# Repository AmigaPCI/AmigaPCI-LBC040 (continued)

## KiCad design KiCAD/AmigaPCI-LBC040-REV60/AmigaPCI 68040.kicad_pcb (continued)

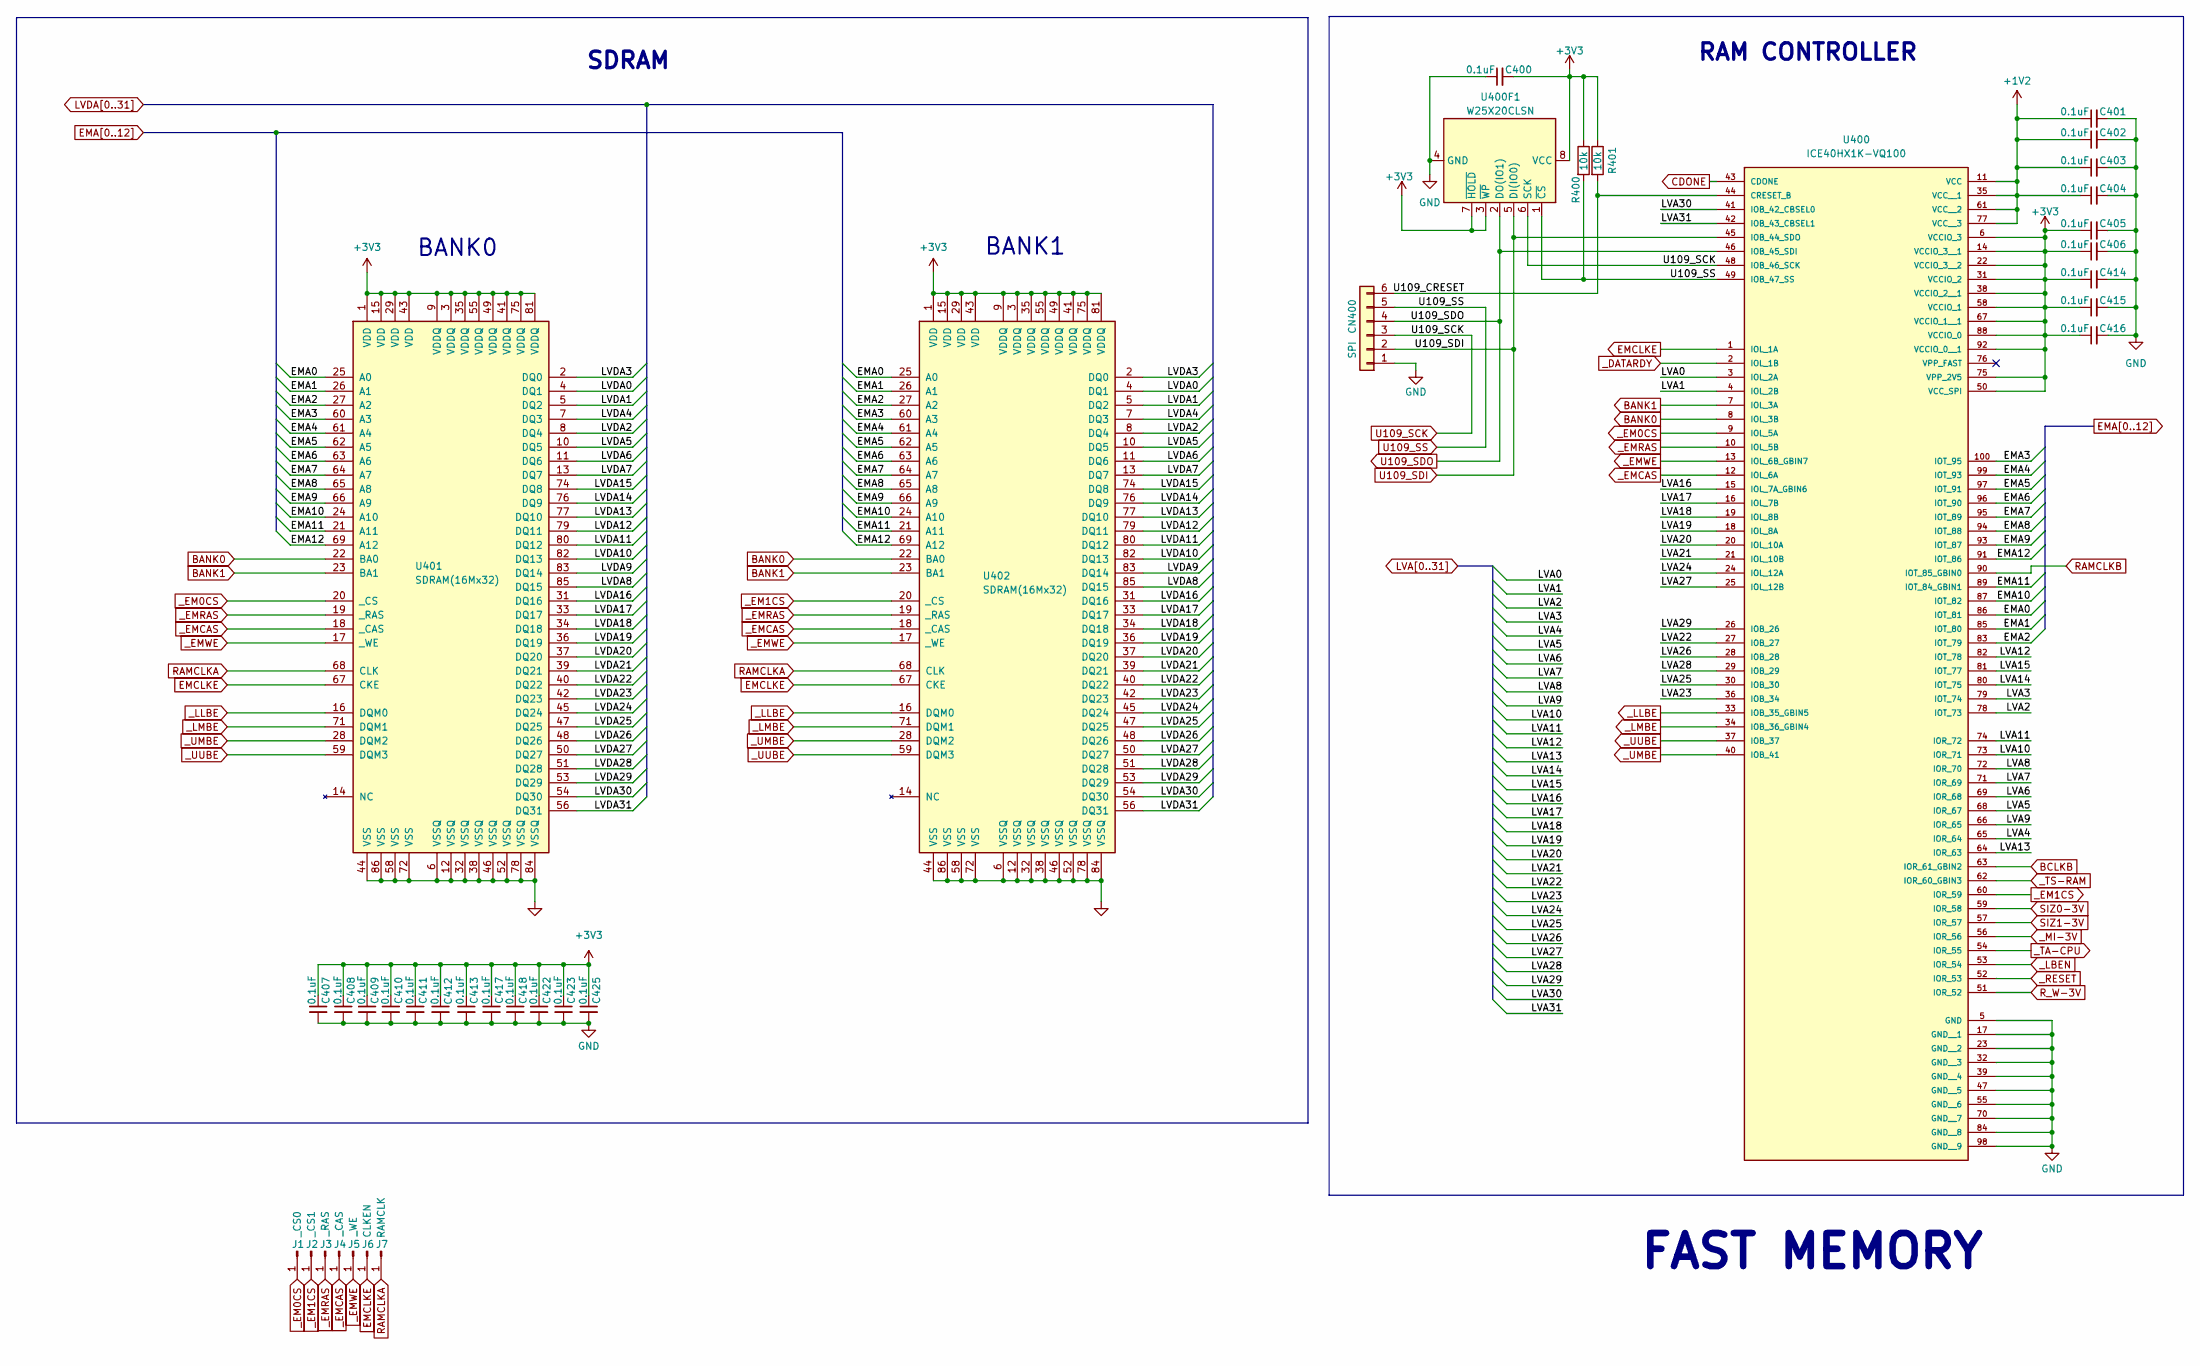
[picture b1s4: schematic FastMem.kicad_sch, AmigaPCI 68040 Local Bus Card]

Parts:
C400, C401, C402, C403, C404, C405, C406, C407, C408, C409, C410, C411, C412, C413, C414, C415, C416, C417, C418, C422, C423, C425: 0.1uF; C_0603_1608Metric; LCSC C14663
CN400: SPI; PinHeader_1x06_P2.54mm_Vertical; LCSC C37208
J1: _CS0; TestPoint_Pad_D1.0mm
J2: _CS1; TestPoint_Pad_D1.0mm
J3: _RAS; TestPoint_Pad_D1.0mm
J4: _CAS; TestPoint_Pad_D1.0mm
J5: _WE; TestPoint_Pad_D1.0mm
J6: CLKEN; TestPoint_Pad_D1.0mm
J7: RAMCLK; TestPoint_Pad_D1.0mm
R400, R401: 10k; R_0603_1608Metric; LCSC C25804
U400: ICE40HX1K-VQ100; LQFP-100_14x14mm_P0.5mm; PARTREV 3.4; LCSC C1519043
U400F1: W25X20CLSN; SOIC-8_3.9x4.9mm_P1.27mm; LCSC C34591
U401, U402: SDRAM(16Mx32); TSOP-II-86; LCSC C17489827

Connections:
+1V2: C401.1, C402.1, C403.1, C404.1, U400.11 (VCC), U400.35 (VCC__1), U400.61 (VCC__2), U400.77 (VCC__3); also elsewhere on the board
+3V3: C400.2, C405.1, C406.1, C407.1, C408.1, C409.1, C410.1, C411.1, C412.1, C413.1, C414.1, C415.1, C416.1, C417.1, C418.1, C422.1, C423.1, C425.1, R400.1, R401.1, U400.6 (VCCIO_3), U400.14 (VCCIO_3__1), U400.22 (VCCIO_3__2), U400.31 (VCCIO_2), U400.38 (VCCIO_2__1), U400.50 (VCC_SPI), U400.58 (VCCIO_1), U400.67 (VCCIO_1__1), U400.75 (VPP_2V5), U400.88 (VCCIO_0), U400.92 (VCCIO_0__1), U400F1.3 (~WP), U400F1.7 (~HOLD), U400F1.8 (VCC), U401.1 (VDD), U401.3 (VDDQ), U401.9 (VDDQ), U401.15 (VDD), U401.29 (VDD), U401.35 (VDDQ), U401.41 (VDDQ), U401.43 (VDD), U401.49 (VDDQ), U401.55 (VDDQ), U401.75 (VDDQ), U401.81 (VDDQ), U402.1 (VDD), U402.3 (VDDQ), U402.9 (VDDQ), U402.15 (VDD), U402.29 (VDD), U402.35 (VDDQ), U402.41 (VDDQ), U402.43 (VDD), U402.49 (VDDQ), U402.55 (VDDQ), U402.75 (VDDQ), U402.81 (VDDQ); also elsewhere on the board
/Fast Memory/U109_CRESET: CN400.6, R401.2, U400.44 (CRESET_B)
BANK0: U400.8 (IOL_3B), U401.22 (BA0), U402.22 (BA0)
BANK1: U400.7 (IOL_3A), U401.23 (BA1), U402.23 (BA1)
BCLKB: U400.63 (IOR_61_GBIN2); also elsewhere on the board
CDONE: U400.43 (CDONE); also elsewhere on the board
EMA0: U400.86 (IOT_81), U401.25 (A0), U402.25 (A0)
EMA1: U400.85 (IOT_80), U401.26 (A1), U402.26 (A1)
EMA2: U400.83 (IOT_79), U401.27 (A2), U402.27 (A2)
EMA3: U400.100 (IOT_95), U401.60 (A3), U402.60 (A3)
EMA4: U400.99 (IOT_93), U401.61 (A4), U402.61 (A4)
EMA5: U400.97 (IOT_91), U401.62 (A5), U402.62 (A5)
EMA6: U400.96 (IOT_90), U401.63 (A6), U402.63 (A6)
EMA7: U400.95 (IOT_89), U401.64 (A7), U402.64 (A7)
EMA8: U400.94 (IOT_88), U401.65 (A8), U402.65 (A8)
EMA9: U400.93 (IOT_87), U401.66 (A9), U402.66 (A9)
EMA10: U400.87 (IOT_82), U401.24 (A10), U402.24 (A10)
EMCLKE: J6.1, U400.1 (IOL_1A), U401.67 (CKE), U402.67 (CKE)
GND: C400.1, C401.2, C402.2, C403.2, C404.2, C405.2, C406.2, C407.2, C408.2, C409.2, C410.2, C411.2, C412.2, C413.2, C414.2, C415.2, C416.2, C417.2, C418.2, C422.2, C423.2, C425.2, CN400.1, U400.5 (GND), U400.17 (GND__1), U400.23 (GND__2), U400.32 (GND__3), U400.39 (GND__4), U400.47 (GND__5), U400.55 (GND__6), U400.70 (GND__7), U400.84 (GND__8), U400.98 (GND__9), U400F1.4 (GND), U401.6 (VSSQ), U401.12 (VSSQ), U401.32 (VSSQ), U401.38 (VSSQ), U401.44 (VSS), U401.46 (VSSQ), U401.52 (VSSQ), U401.58 (VSS), U401.72 (VSS), U401.78 (VSSQ), U401.84 (VSSQ), U401.86 (VSS), U402.6 (VSSQ), U402.12 (VSSQ), U402.32 (VSSQ), U402.38 (VSSQ), U402.44 (VSS), U402.46 (VSSQ), U402.52 (VSSQ), U402.58 (VSS), U402.72 (VSS), U402.78 (VSSQ), U402.84 (VSSQ), U402.86 (VSS); also elsewhere on the board
LVA0: U400.3 (IOL_2A); also elsewhere on the board
LVA1: U400.4 (IOL_2B); also elsewhere on the board
LVA2: U400.78 (IOT_73); also elsewhere on the board
LVA3: U400.79 (IOT_74); also elsewhere on the board
LVA4: U400.65 (IOR_64); also elsewhere on the board
LVA5: U400.68 (IOR_67); also elsewhere on the board
LVA6: U400.69 (IOR_68); also elsewhere on the board
LVA7: U400.71 (IOR_69); also elsewhere on the board
LVA8: U400.72 (IOR_70); also elsewhere on the board
LVA9: U400.66 (IOR_65); also elsewhere on the board
LVA10: U400.73 (IOR_71); also elsewhere on the board
LVA11: U400.74 (IOR_72); also elsewhere on the board
LVA12: U400.82 (IOT_78); also elsewhere on the board
LVA13: U400.64 (IOR_63); also elsewhere on the board
LVA14: U400.80 (IOT_75); also elsewhere on the board
LVA15: U400.81 (IOT_77); also elsewhere on the board
LVA16: U400.15 (IOL_7A_GBIN6); also elsewhere on the board
LVA17: U400.16 (IOL_7B); also elsewhere on the board
LVA18: U400.19 (IOL_8B); also elsewhere on the board
LVA19: U400.18 (IOL_8A); also elsewhere on the board
LVA20: U400.20 (IOL_10A); also elsewhere on the board
LVA21: U400.21 (IOL_10B); also elsewhere on the board
LVA22: U400.27 (IOB_27); also elsewhere on the board
LVA23: U400.36 (IOB_34); also elsewhere on the board
LVA24: U400.24 (IOL_12A); also elsewhere on the board
LVA25: U400.30 (IOB_30); also elsewhere on the board
LVA26: U400.28 (IOB_28); also elsewhere on the board
LVA27: U400.25 (IOL_12B); also elsewhere on the board
LVA28: U400.29 (IOB_29); also elsewhere on the board
LVA29: U400.26 (IOB_26); also elsewhere on the board
LVA30: U400.41 (IOB_42_CBSEL0); also elsewhere on the board
LVA31: U400.42 (IOB_43_CBSEL1); also elsewhere on the board
LVDA0: U401.4 (DQ1), U402.4 (DQ1); also elsewhere on the board
LVDA1: U401.5 (DQ2), U402.5 (DQ2); also elsewhere on the board
LVDA2: U401.8 (DQ4), U402.8 (DQ4); also elsewhere on the board
LVDA3: U401.2 (DQ0), U402.2 (DQ0); also elsewhere on the board
LVDA4: U401.7 (DQ3), U402.7 (DQ3); also elsewhere on the board
LVDA5: U401.10 (DQ5), U402.10 (DQ5); also elsewhere on the board
LVDA6: U401.11 (DQ6), U402.11 (DQ6); also elsewhere on the board
LVDA7: U401.13 (DQ7), U402.13 (DQ7); also elsewhere on the board
LVDA8: U401.85 (DQ15), U402.85 (DQ15); also elsewhere on the board
LVDA9: U401.83 (DQ14), U402.83 (DQ14); also elsewhere on the board
LVDA10: U401.82 (DQ13), U402.82 (DQ13); also elsewhere on the board
LVDA11: U401.80 (DQ12), U402.80 (DQ12); also elsewhere on the board
LVDA12: U401.79 (DQ11), U402.79 (DQ11); also elsewhere on the board
LVDA13: U401.77 (DQ10), U402.77 (DQ10); also elsewhere on the board
LVDA14: U401.76 (DQ9), U402.76 (DQ9); also elsewhere on the board
LVDA15: U401.74 (DQ8), U402.74 (DQ8); also elsewhere on the board
LVDA16: U401.31 (DQ16), U402.31 (DQ16); also elsewhere on the board
LVDA17: U401.33 (DQ17), U402.33 (DQ17); also elsewhere on the board
LVDA18: U401.34 (DQ18), U402.34 (DQ18); also elsewhere on the board
LVDA19: U401.36 (DQ19), U402.36 (DQ19); also elsewhere on the board
LVDA20: U401.37 (DQ20), U402.37 (DQ20); also elsewhere on the board
LVDA21: U401.39 (DQ21), U402.39 (DQ21); also elsewhere on the board
LVDA22: U401.40 (DQ22), U402.40 (DQ22); also elsewhere on the board
LVDA23: U401.42 (DQ23), U402.42 (DQ23); also elsewhere on the board
LVDA24: U401.45 (DQ24), U402.45 (DQ24); also elsewhere on the board
LVDA25: U401.47 (DQ25), U402.47 (DQ25); also elsewhere on the board
LVDA26: U401.48 (DQ26), U402.48 (DQ26); also elsewhere on the board
LVDA27: U401.50 (DQ27), U402.50 (DQ27); also elsewhere on the board
LVDA28: U401.51 (DQ28), U402.51 (DQ28); also elsewhere on the board
LVDA29: U401.53 (DQ29), U402.53 (DQ29); also elsewhere on the board
LVDA30: U401.54 (DQ30), U402.54 (DQ30); also elsewhere on the board
LVDA31: U401.56 (DQ31), U402.56 (DQ31); also elsewhere on the board
RAMCLKA: J7.1, U401.68 (CLK), U402.68 (CLK); also elsewhere on the board
RAMCLKB: U400.90 (IOT_85_GBIN0); also elsewhere on the board
R_W-3V: U400.51 (IOR_52); also elsewhere on the board
SIZ0-3V: U400.59 (IOR_58); also elsewhere on the board
SIZ1-3V: U400.57 (IOR_57); also elsewhere on the board
U109_SCK: CN400.3, U400.48 (IOB_46_SCK), U400F1.6 (SCK); also elsewhere on the board
U109_SDI: CN400.2, U400.45 (IOB_44_SDO), U400F1.5 (DI(IO0)); also elsewhere on the board
U109_SDO: CN400.4, U400.46 (IOB_45_SDI), U400F1.2 (DO(IO1)); also elsewhere on the board
U109_SS: CN400.5, R400.2, U400.49 (IOB_47_SS), U400F1.1 (~CS); also elsewhere on the board
_DATARDY: U400.2 (IOL_1B); also elsewhere on the board
_EM0CS: J1.1, U400.9 (IOL_5A), U401.20 (_CS)
_EM1CS: J2.1, U400.60 (IOR_59), U402.20 (_CS)
_EMCAS: J4.1, U400.12 (IOL_6A), U401.18 (_CAS), U402.18 (_CAS)
_EMRAS: J3.1, U400.10 (IOL_5B), U401.19 (_RAS), U402.19 (_RAS)
_EMWE: J5.1, U400.13 (IOL_6B_GBIN7), U401.17 (_WE), U402.17 (_WE)
_LBEN: U400.53 (IOR_54); also elsewhere on the board
_LLBE: U400.33 (IOB_35_GBIN5), U401.16 (DQM0), U402.16 (DQM0)
_LMBE: U400.34 (IOB_36_GBIN4), U401.71 (DQM1), U402.71 (DQM1)
_MI-3V: U400.56 (IOR_56); also elsewhere on the board
_RESET: U400.52 (IOR_53); also elsewhere on the board
_TA-CPU: U400.54 (IOR_55); also elsewhere on the board
_TS-RAM: U400.62 (IOR_60_GBIN3); also elsewhere on the board
_UMBE: U400.40 (IOB_41), U401.28 (DQM2), U402.28 (DQM2)
_UUBE: U400.37 (IOB_37), U401.59 (DQM3), U402.59 (DQM3)

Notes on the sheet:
RAM CONTROLLER
FAST MEMORY
BANK0
SDRAM
BANK1

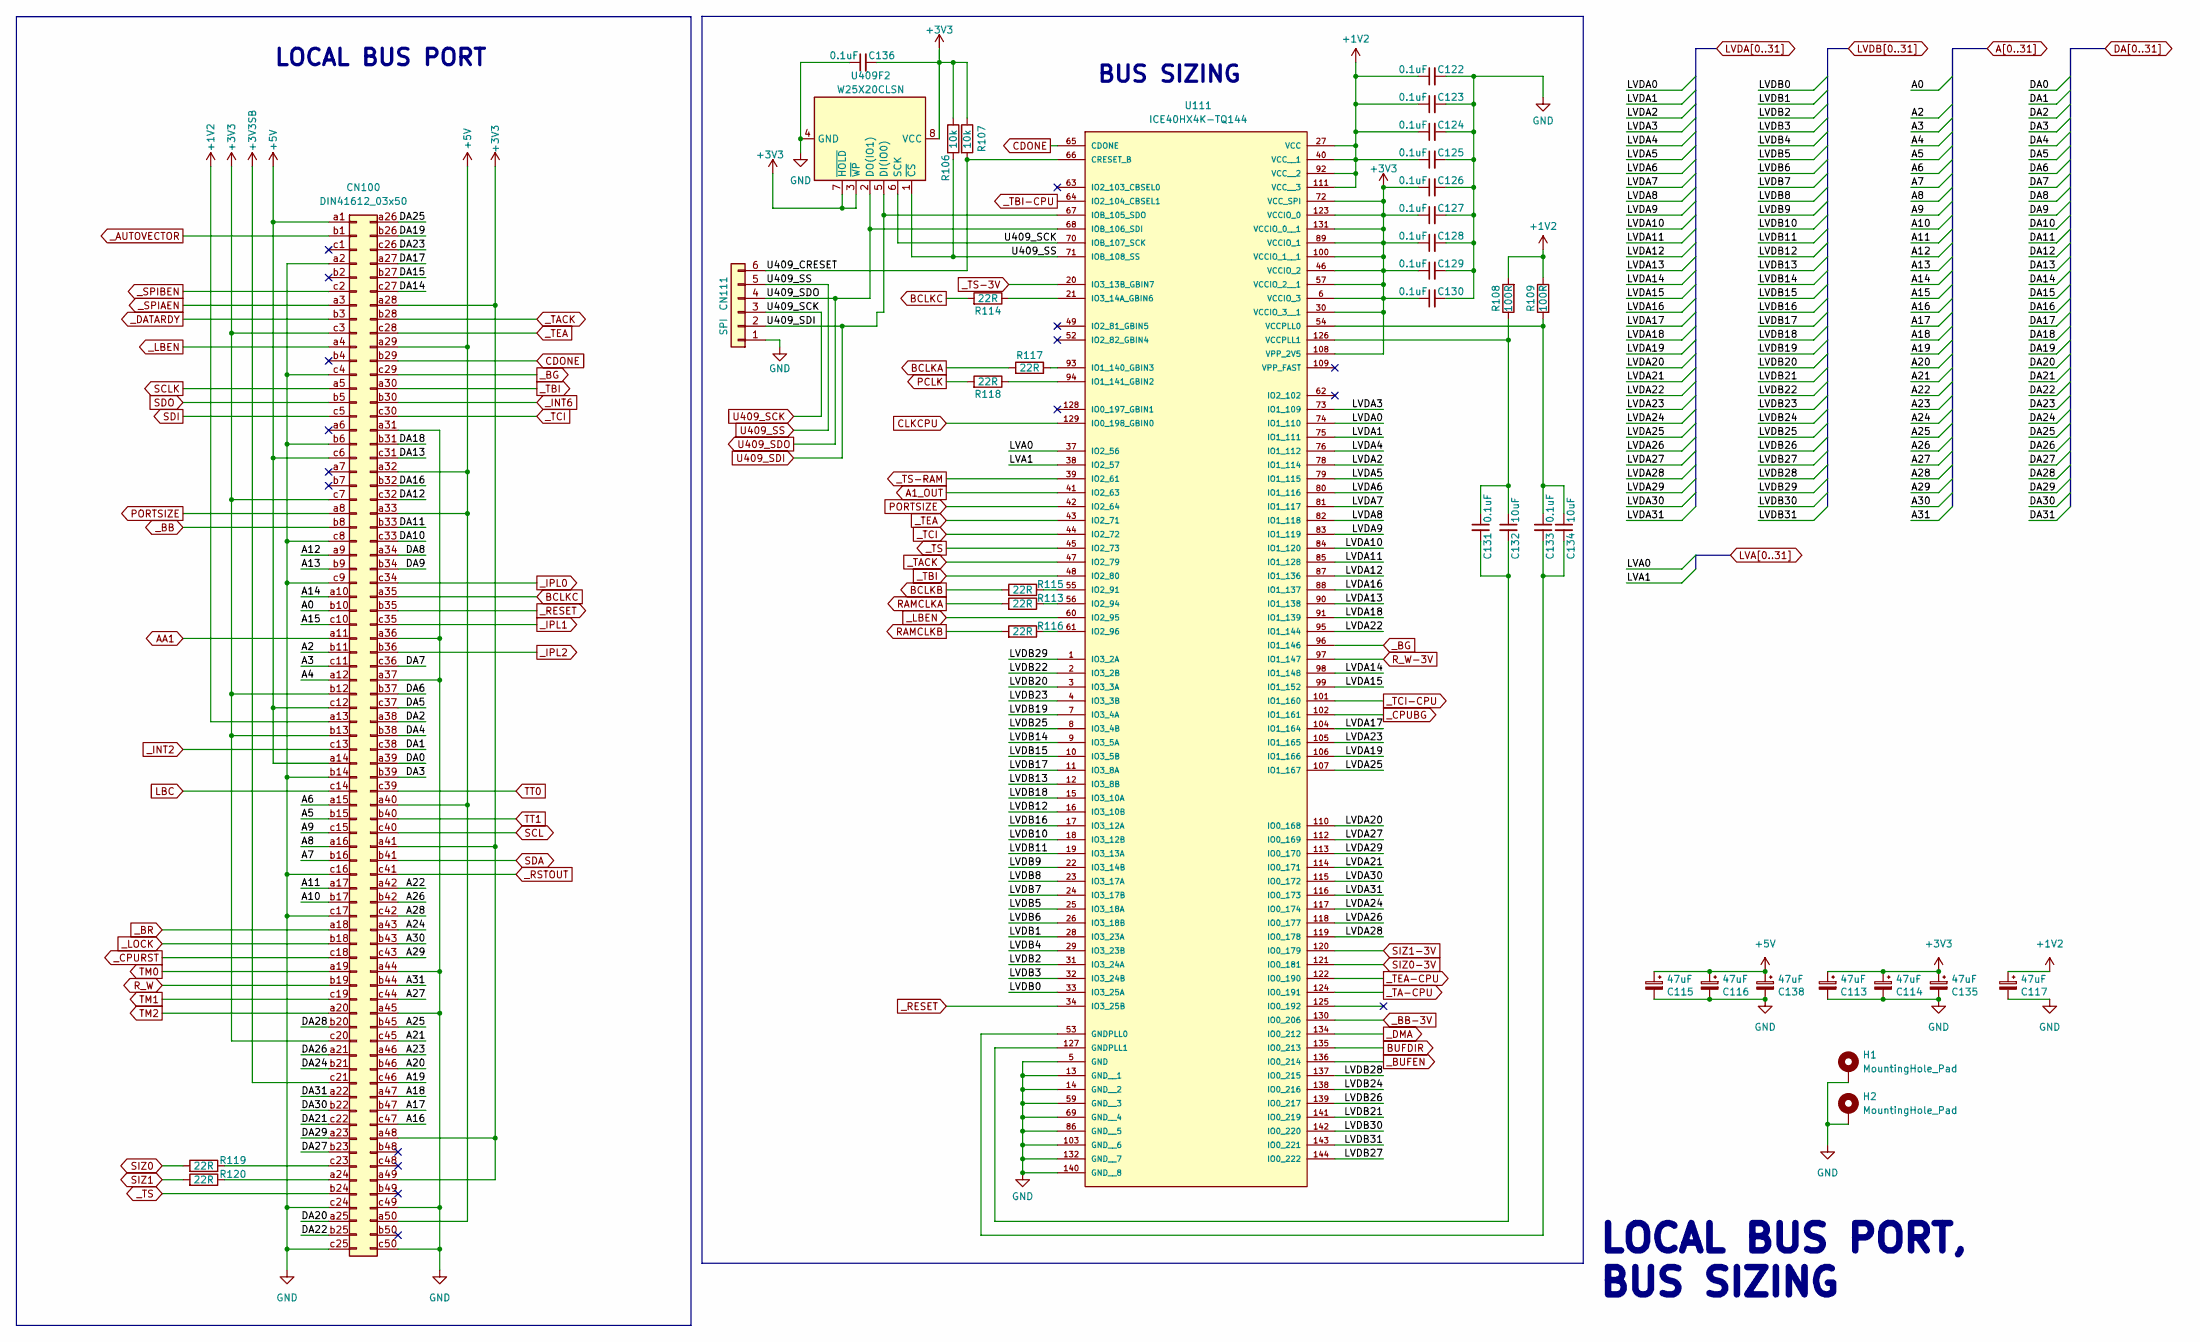
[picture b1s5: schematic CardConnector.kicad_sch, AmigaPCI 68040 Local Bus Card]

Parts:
C113, C114, C115, C116, C117, C135, C138: 47uF; CP_Radial_D5.0mm_P2.00mm; LCSC C88724
C122, C123, C124, C125, C126, C127, C128, C129, C130, C131, C133, C136: 0.1uF; C_0603_1608Metric; LCSC C14663
C132, C134: 10uF; C_0603_1608Metric; LCSC C96446
CN100: DIN41612_03x50; DIN41612_C_3x50_Male_Vertical_THT; LCSC C3654550
CN111: SPI; PinHeader_1x06_P2.54mm_Vertical; LCSC C37208
H1, H2: MountingHole_Pad; MountingHole_3.5mm_Pad
R106, R107: 10k; R_0603_1608Metric; LCSC C25804
R108, R109: 100R; R_0603_1608Metric; LCSC C22775
R113, R114, R115, R116, R117, R118, R119, R120: 22R; R_0603_1608Metric; LCSC C23345
U111: ICE40HX4K-TQ144; LQFP-144_20x20mm_P0.5mm; LCSC C1521989
U409F2: W25X20CLSN; SOIC-8_3.9x4.9mm_P1.27mm; LCSC C34591

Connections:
+1V2: C117.1, C122.1, C123.1, C124.1, C125.1, CN100.a13, R108.2, R109.1, U111.27 (VCC), U111.40 (VCC__1), U111.92 (VCC__2), U111.111 (VCC__3); also elsewhere on the board
+3V3: C113.1, C114.1, C126.1, C127.1, C128.1, C129.1, C130.1, C135.1, C136.2, CN100.a28, CN100.a41, CN100.a48, CN100.a49, CN100.b12, CN100.b13, CN100.c3, CN100.c7, CN100.c20, R106.1, R107.1, U111.6 (VCCIO_3), U111.30 (VCCIO_3__1), U111.46 (VCCIO_2), U111.57 (VCCIO_2__1), U111.72 (VCC_SPI), U111.89 (VCCIO_1), U111.100 (VCCIO_1__1), U111.108 (VPP_2V5), U111.123 (VCCIO_0), U111.131 (VCCIO_0__1), U409F2.3 (~WP), U409F2.7 (~HOLD), U409F2.8 (VCC); also elsewhere on the board
+3V3SB: CN100.c21
+5V: C115.1, C116.1, C138.1, CN100.a1, CN100.a14, CN100.a29, CN100.a32, CN100.a33, CN100.a40, CN100.a50, CN100.c6, CN100.c12; also elsewhere on the board
/Card Connector/U409_CRESET: CN111.6, R107.2, U111.66 (CRESET_B)
A0: CN100.b10; also elsewhere on the board
A1_OUT: U111.41 (IO2_63); also elsewhere on the board
A2: CN100.b11; also elsewhere on the board
A3: CN100.c11; also elsewhere on the board
A4: CN100.a12; also elsewhere on the board
A5: CN100.b15; also elsewhere on the board
A6: CN100.a15; also elsewhere on the board
A7: CN100.b16; also elsewhere on the board
A8: CN100.a16; also elsewhere on the board
A9: CN100.c15; also elsewhere on the board
A10: CN100.b17; also elsewhere on the board
A11: CN100.a17; also elsewhere on the board
A12: CN100.a9; also elsewhere on the board
A13: CN100.b9; also elsewhere on the board
A14: CN100.a10; also elsewhere on the board
A15: CN100.c10; also elsewhere on the board
A16: CN100.c47; also elsewhere on the board
A17: CN100.b47; also elsewhere on the board
A18: CN100.a47; also elsewhere on the board
A19: CN100.c46; also elsewhere on the board
A20: CN100.b46; also elsewhere on the board
A21: CN100.c45; also elsewhere on the board
A22: CN100.a42; also elsewhere on the board
A23: CN100.a46; also elsewhere on the board
A24: CN100.a43; also elsewhere on the board
A25: CN100.b45; also elsewhere on the board
A26: CN100.b42; also elsewhere on the board
A27: CN100.c44; also elsewhere on the board
A28: CN100.c42; also elsewhere on the board
A29: CN100.c43; also elsewhere on the board
A30: CN100.b43; also elsewhere on the board
A31: CN100.b44; also elsewhere on the board
AA1: CN100.a11; also elsewhere on the board
BCLKA: R117.2; also elsewhere on the board
BCLKB: R115.2; also elsewhere on the board
BCLKC: CN100.a35, R114.2
BUFDIR: U111.135 (IO0_213); also elsewhere on the board
CDONE: CN100.b29, U111.65 (CDONE); also elsewhere on the board
CLKCPU: U111.129 (IO0_198_GBIN0); also elsewhere on the board
DA0: CN100.a39; also elsewhere on the board
DA1: CN100.c38; also elsewhere on the board
DA2: CN100.a38; also elsewhere on the board
DA3: CN100.b39; also elsewhere on the board
DA4: CN100.b38; also elsewhere on the board
DA5: CN100.c37; also elsewhere on the board
DA6: CN100.b37; also elsewhere on the board
DA7: CN100.c36; also elsewhere on the board
DA8: CN100.a34; also elsewhere on the board
DA9: CN100.b34; also elsewhere on the board
DA10: CN100.c33; also elsewhere on the board
DA11: CN100.b33; also elsewhere on the board
DA12: CN100.c32; also elsewhere on the board
DA13: CN100.c31; also elsewhere on the board
DA14: CN100.c27; also elsewhere on the board
DA15: CN100.b27; also elsewhere on the board
DA16: CN100.b32; also elsewhere on the board
DA17: CN100.a27; also elsewhere on the board
DA18: CN100.b31; also elsewhere on the board
DA19: CN100.b26; also elsewhere on the board
DA20: CN100.a25; also elsewhere on the board
DA21: CN100.c22; also elsewhere on the board
DA22: CN100.b25; also elsewhere on the board
DA23: CN100.c26; also elsewhere on the board
DA24: CN100.b21; also elsewhere on the board
DA25: CN100.a26; also elsewhere on the board
DA26: CN100.a21; also elsewhere on the board
DA27: CN100.b23; also elsewhere on the board
DA28: CN100.b20; also elsewhere on the board
DA29: CN100.a23; also elsewhere on the board
DA30: CN100.b22; also elsewhere on the board
DA31: CN100.a22; also elsewhere on the board
GND: C113.2, C114.2, C115.2, C116.2, C117.2, C122.2, C123.2, C124.2, C125.2, C126.2, C127.2, C128.2, C129.2, C130.2, C135.2, C136.1, C138.2, CN100.a2, CN100.a31, CN100.a36, CN100.a37, CN100.a44, CN100.a45, CN100.b6, CN100.b14, CN100.c4, CN100.c8, CN100.c9, CN100.c16, CN100.c17, CN100.c24, CN100.c25, CN100.c49, CN100.c50, CN111.1, H1.1, H2.1, U111.5 (GND), U111.13 (GND__1), U111.14 (GND__2), U111.59 (GND__3), U111.69 (GND__4), U111.86 (GND__5), U111.103 (GND__6), U111.132 (GND__7), U111.140 (GND__8), U409F2.4 (GND); also elsewhere on the board
LBC: CN100.c14
LVA0: U111.37 (IO2_56); also elsewhere on the board
LVA1: U111.38 (IO2_57); also elsewhere on the board
LVDA0: U111.74 (IO1_110); also elsewhere on the board
LVDA1: U111.75 (IO1_111); also elsewhere on the board
LVDA2: U111.78 (IO1_114); also elsewhere on the board
LVDA3: U111.73 (IO1_109); also elsewhere on the board
LVDA4: U111.76 (IO1_112); also elsewhere on the board
LVDA5: U111.79 (IO1_115); also elsewhere on the board
LVDA6: U111.80 (IO1_116); also elsewhere on the board
LVDA7: U111.81 (IO1_117); also elsewhere on the board
LVDA8: U111.82 (IO1_118); also elsewhere on the board
LVDA9: U111.83 (IO1_119); also elsewhere on the board
LVDA10: U111.84 (IO1_120); also elsewhere on the board
LVDA11: U111.85 (IO1_128); also elsewhere on the board
LVDA12: U111.87 (IO1_136); also elsewhere on the board
LVDA13: U111.90 (IO1_138); also elsewhere on the board
LVDA14: U111.98 (IO1_148); also elsewhere on the board
LVDA15: U111.99 (IO1_152); also elsewhere on the board
LVDA16: U111.88 (IO1_137); also elsewhere on the board
LVDA17: U111.104 (IO1_164); also elsewhere on the board
LVDA18: U111.91 (IO1_139); also elsewhere on the board
LVDA19: U111.106 (IO1_166); also elsewhere on the board
LVDA20: U111.110 (IO0_168); also elsewhere on the board
LVDA21: U111.114 (IO0_171); also elsewhere on the board
LVDA22: U111.95 (IO1_144); also elsewhere on the board
LVDA23: U111.105 (IO1_165); also elsewhere on the board
LVDA24: U111.117 (IO0_174); also elsewhere on the board
LVDA25: U111.107 (IO1_167); also elsewhere on the board
LVDA26: U111.118 (IO0_177); also elsewhere on the board
LVDA27: U111.112 (IO0_169); also elsewhere on the board
LVDA28: U111.119 (IO0_178); also elsewhere on the board
LVDA29: U111.113 (IO0_170); also elsewhere on the board
LVDA30: U111.115 (IO0_172); also elsewhere on the board
LVDA31: U111.116 (IO0_173); also elsewhere on the board
LVDB0: U111.33 (IO3_25A); also elsewhere on the board
LVDB1: U111.28 (IO3_23A); also elsewhere on the board
LVDB2: U111.31 (IO3_24A); also elsewhere on the board
LVDB3: U111.32 (IO3_24B); also elsewhere on the board
LVDB4: U111.29 (IO3_23B); also elsewhere on the board
LVDB5: U111.25 (IO3_18A); also elsewhere on the board
LVDB6: U111.26 (IO3_18B); also elsewhere on the board
LVDB7: U111.24 (IO3_17B); also elsewhere on the board
LVDB8: U111.23 (IO3_17A); also elsewhere on the board
LVDB9: U111.22 (IO3_14B); also elsewhere on the board
LVDB10: U111.18 (IO3_12B); also elsewhere on the board
LVDB11: U111.19 (IO3_13A); also elsewhere on the board
LVDB12: U111.16 (IO3_10B); also elsewhere on the board
LVDB13: U111.12 (IO3_8B); also elsewhere on the board
LVDB14: U111.9 (IO3_5A); also elsewhere on the board
LVDB15: U111.10 (IO3_5B); also elsewhere on the board
LVDB16: U111.17 (IO3_12A); also elsewhere on the board
LVDB17: U111.11 (IO3_8A); also elsewhere on the board
LVDB18: U111.15 (IO3_10A); also elsewhere on the board
LVDB19: U111.7 (IO3_4A); also elsewhere on the board
LVDB20: U111.3 (IO3_3A); also elsewhere on the board
LVDB21: U111.141 (IO0_219); also elsewhere on the board
LVDB22: U111.2 (IO3_2B); also elsewhere on the board
LVDB23: U111.4 (IO3_3B); also elsewhere on the board
LVDB24: U111.138 (IO0_216); also elsewhere on the board
LVDB25: U111.8 (IO3_4B); also elsewhere on the board
LVDB26: U111.139 (IO0_217); also elsewhere on the board
LVDB27: U111.144 (IO0_222); also elsewhere on the board
LVDB28: U111.137 (IO0_215); also elsewhere on the board
LVDB29: U111.1 (IO3_2A); also elsewhere on the board
LVDB30: U111.142 (IO0_220); also elsewhere on the board
LVDB31: U111.143 (IO0_221); also elsewhere on the board
unnamed: CN100.a24, R120.1
unnamed: CN100.c23, R119.1
unnamed: C133.2, C134.2, U111.53 (GNDPLL0)
unnamed: C131.2, C132.2, U111.127 (GNDPLL1)
unnamed: R117.1, U111.93 (IO1_140_GBIN3)
unnamed: R118.1, U111.94 (IO1_141_GBIN2)
unnamed: R115.1, U111.55 (IO2_91)
unnamed: R113.1, U111.56 (IO2_94)
unnamed: R116.1, U111.61 (IO2_96)
unnamed: R114.1, U111.21 (IO3_14A_GBIN6)
unnamed: C133.1, C134.1, R109.2, U111.54 (VCCPLL0)
unnamed: C131.1, C132.1, R108.1, U111.126 (VCCPLL1)
PCLK: R118.2; also elsewhere on the board
PORTSIZE: CN100.a8, U111.42 (IO2_64)
RAMCLKA: R113.2; also elsewhere on the board
RAMCLKB: R116.2; also elsewhere on the board
R_W: CN100.b19; also elsewhere on the board
R_W-3V: U111.97 (IO1_147); also elsewhere on the board
SCL: CN100.c40
SCLK: CN100.a5; also elsewhere on the board
SDA: CN100.b41
SDI: CN100.c5; also elsewhere on the board
SDO: CN100.b5; also elsewhere on the board
SIZ0: R119.2; also elsewhere on the board
SIZ0-3V: U111.121 (IO0_181); also elsewhere on the board
SIZ1: R120.2; also elsewhere on the board
SIZ1-3V: U111.120 (IO0_179); also elsewhere on the board
TM0: CN100.a19; also elsewhere on the board
TM1: CN100.c19; also elsewhere on the board
TM2: CN100.a20; also elsewhere on the board
TT0: CN100.c39; also elsewhere on the board
TT1: CN100.b40; also elsewhere on the board
U409_SCK: CN111.3, U111.70 (IOB_107_SCK), U409F2.6 (SCK); also elsewhere on the board
U409_SDI: CN111.2, U111.67 (IOB_105_SDO), U409F2.5 (DI(IO0)); also elsewhere on the board
U409_SDO: CN111.4, U111.68 (IOB_106_SDI), U409F2.2 (DO(IO1)); also elsewhere on the board
U409_SS: CN111.5, R106.2, U111.71 (IOB_108_SS), U409F2.1 (~CS); also elsewhere on the board
_AUTOVECTOR: CN100.b1; also elsewhere on the board
_BB: CN100.b8; also elsewhere on the board
_BB-3V: U111.130 (IO0_206); also elsewhere on the board
_BG: CN100.c29, U111.96 (IO1_146); also elsewhere on the board
_BR: CN100.a18; also elsewhere on the board
_BUFEN: U111.136 (IO0_214); also elsewhere on the board
_CPUBG: U111.102 (IO1_161); also elsewhere on the board
_CPURST: CN100.c18; also elsewhere on the board
_DATARDY: CN100.b3; also elsewhere on the board
_DMA: U111.134 (IO0_212); also elsewhere on the board
_INT2: CN100.c13
_INT6: CN100.b30
_IPL0: CN100.c34; also elsewhere on the board
_IPL1: CN100.c35; also elsewhere on the board
_IPL2: CN100.b36; also elsewhere on the board
_LBEN: CN100.a4, U111.60 (IO2_95); also elsewhere on the board
_LOCK: CN100.b18; also elsewhere on the board
_RESET: CN100.b35, U111.34 (IO3_25B); also elsewhere on the board
_RSTOUT: CN100.c41; also elsewhere on the board
_SPIAEN: CN100.a3; also elsewhere on the board
_SPIBEN: CN100.c2; also elsewhere on the board
_TA-CPU: U111.124 (IO0_191); also elsewhere on the board
_TACK: CN100.b28, U111.47 (IO2_79)
_TBI: CN100.a30, U111.48 (IO2_80)
_TBI-CPU: U111.64 (IO2_104_CBSEL1); also elsewhere on the board
_TCI: CN100.c30, U111.44 (IO2_72)
_TCI-CPU: U111.101 (IO1_160); also elsewhere on the board
_TEA: CN100.c28, U111.43 (IO2_71)
_TEA-CPU: U111.122 (IO0_190); also elsewhere on the board
_TS: CN100.b24, U111.45 (IO2_73)
_TS-3V: U111.20 (IO3_13B_GBIN7); also elsewhere on the board
_TS-RAM: U111.39 (IO2_61); also elsewhere on the board

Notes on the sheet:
BUS SIZING
LOCAL BUS PORT, BUS SIZING
LOCAL BUS PORT

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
